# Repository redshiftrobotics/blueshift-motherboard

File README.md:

# blueshift-motherboard
Blueshift Robotics Motherboard Design Files

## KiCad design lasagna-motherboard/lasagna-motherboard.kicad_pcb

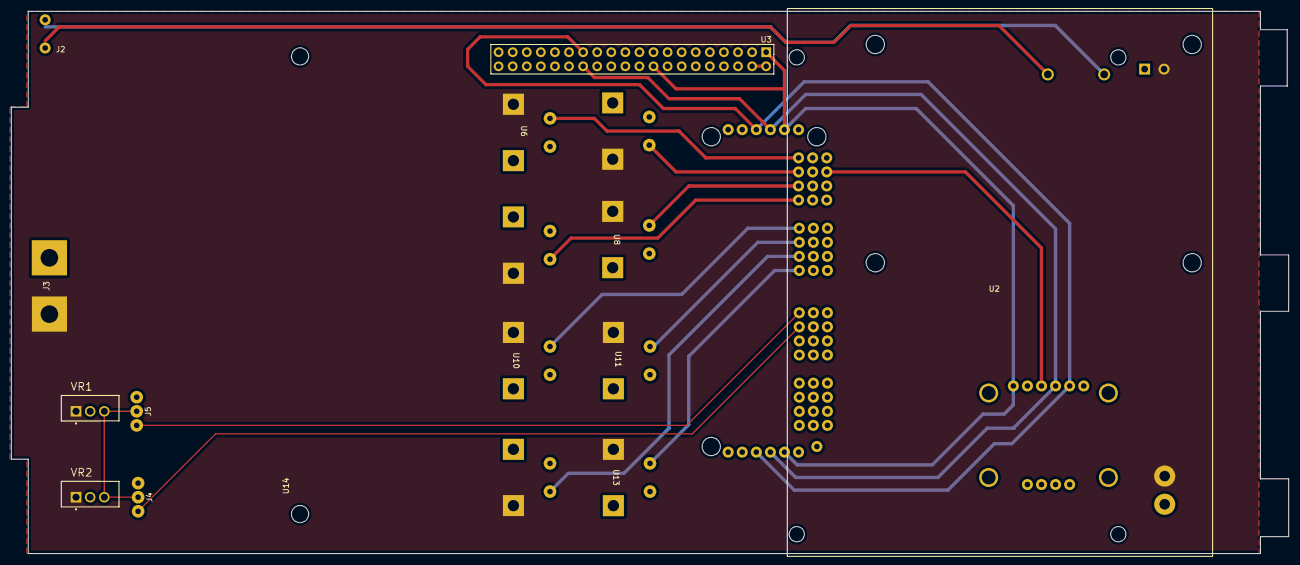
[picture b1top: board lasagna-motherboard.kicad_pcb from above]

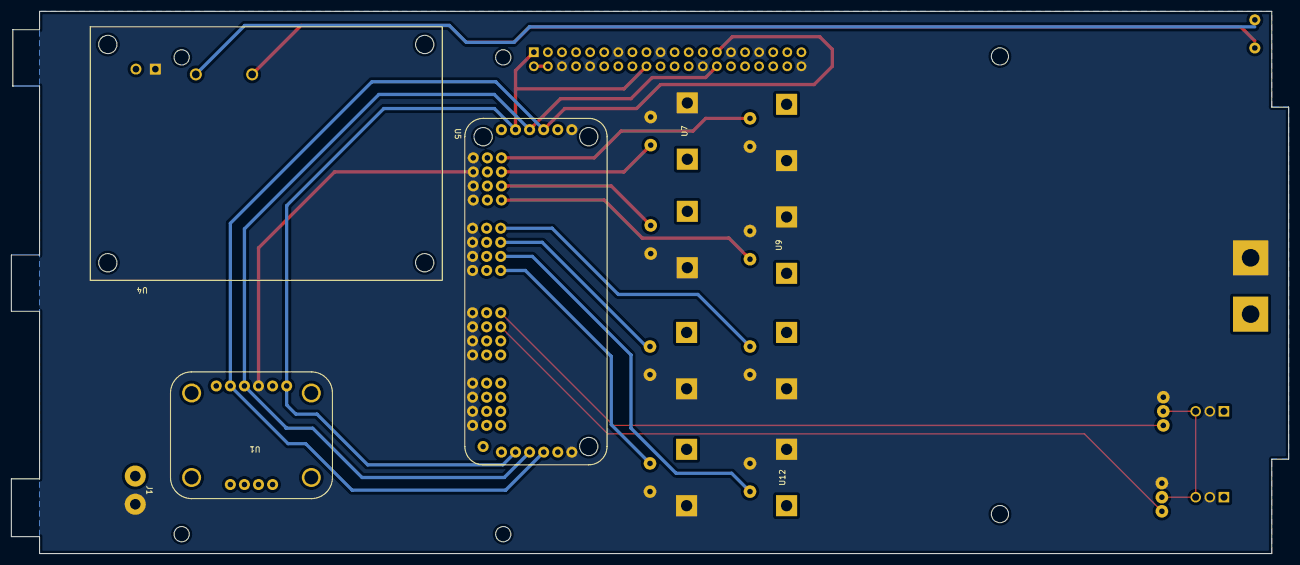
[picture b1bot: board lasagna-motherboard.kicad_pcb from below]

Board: 2 copper layers, 230.4 x 97.8 mm, 21 parts (7 on the bottom side), 18 nets.

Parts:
J1: Jetson_Power_Connector; Jetson Power Connector
J2: Fathom_X_Connector; FathomX_Connector
J3: Power_Connector
J4, J5: Servo_Connector; Servo PWM Connector
U1: Adafruit_BNO055_IMU
U2: Jetson_Xavier_NX_Mounting_Holes
U3: Jetson_Xavier_NX_Pins; Jetson_Xavier_NX_2X20_Pin_Header
U4: FathomX
U5: Adafruit_PCA9685_PWMGen
U6, U7, U8, U9, U10, U11, U12, U13: ESC
U14: ESC_Holder_Mounting_Holes; ESC Holder mounting Holes
VR1, VR2: 7805_TO-220_Voltage_Regulator; Voltage Regulator TO255

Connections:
+3V3: U1.5 (VIN), U3.1 (3V3), U3.17 (3V3), U5.5 (VCC), U5.11 (VCC)
+5V: J4.2 (VIN), J5.2 (VIN), U3.2 (5V), U3.4 (5V), VR1.3 (VOUT), VR2.3 (VOUT)
+12V: J1.1 (VIN), J3.1 (VIN), U4.4 (VIN), U6.1 (VIN), U7.1 (VIN), U8.1 (VIN), U9.1 (VIN), U10.1 (VIN), U11.1 (VIN), U12.1 (VIN), U13.1 (VIN), VR1.1 (VIN), VR2.1 (VIN)
GND: J1.2 (GND), J3.2 (GND), J4.3 (GND), J5.3 (GND), U1.7 (GND), U3.6 (GND), U3.9 (GND), U3.14 (GND), U3.20 (GND), U3.25 (GND), U3.30 (GND), U3.34 (GND), U3.39 (GND), U4.3 (GND), U5.1 (GND), U5.7 (GND), U5.15 (GND), U5.18 (GND), U5.21 (GND), U5.24 (GND), U5.27 (GND), U5.30 (GND), U5.33 (GND), U5.36 (GND), U5.39 (GND), U5.42 (GND), U5.45 (GND), U5.48 (GND), U5.51 (GND), U5.54 (GND), U5.57 (GND), U5.60 (GND), U6.2 (GND), U6.4 (PWM_GND), U7.2 (GND), U7.4 (PWM_GND), U8.2 (GND), U8.4 (PWM_GND), U9.2 (GND), U9.4 (PWM_GND), U10.2 (GND), U10.4 (PWM_GND), U11.2 (GND), U11.4 (PWM_GND), U12.2 (GND), U12.4 (PWM_GND), U13.2 (GND), U13.4 (PWM_GND), VR1.2 (GND), VR2.2 (GND)
unnamed: J2.1 (PL_L), U4.1 (PL_L)
unnamed: J2.2 (HV_SIG), U4.2 (HV_SIG)
unnamed: U1.8 (SDA), U3.27 (I2C0_SDA), U5.4 (SDA), U5.10 (SDA)
unnamed: U1.9 (SCL), U3.28 (I2C0_SCL), U5.3 (SCL), U5.9 (SCL)
unnamed: U5.13 (PWM0), U6.3 (PWM)
unnamed: U5.16 (PWM1), U7.3 (PWM)
unnamed: U5.19 (PWM2), U8.3 (PWM)
unnamed: U5.22 (PWM3), U9.3 (PWM)
unnamed: J5.1 (PWM), U5.37 (PWM8)
unnamed: J4.1 (PWM), U5.40 (PWM9)
unnamed: U5.25 (PWM4), U10.3 (PWM)
unnamed: U5.28 (PWM5), U11.3 (PWM)
unnamed: U5.31 (PWM6), U12.3 (PWM)
unnamed: U5.34 (PWM7), U13.3 (PWM)

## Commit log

2021-04-14 Test version control
2021-04-18 introducing Colin the Motherboard :)
2021-04-21 changed schematic symbol, begain schematic layout
2021-04-24 finish first pass at schematic, errors not fully resolved yet
2021-05-12 finish first draft of Colin 1.0, connect molex connectors directly, add capacitors but expect to solder directly to the ESCs, add 3V3 miniplane
2021-05-13 create active BOM
2021-05-13 Combine duplicate connectors, remove old test schematic file
2021-05-13 Update pcb board shape to make room for main power connector
2021-05-14 Revert "Update pcb board shape to make room for main power connector"
    This reverts commit 495c49e4263b1bc1385d283c099a491fd0e220ab.
2021-05-14 finish draft of Colin v1.0! Clear DRC violations, adjust silkscreen
2021-05-14 Add outjob files
2021-05-14 Update 2 pos connector component descriptions
2021-05-14 Add schematic symbols for jetson and esc mounting holes
2021-05-14 Remove mechanical components from BOM
2021-05-14 eliminate dumb part of 3v3 polygon
2021-05-14 Colin Motherboard v1.0 Release
    Update outjob files to combine gerbers and nc drill into one folder that can be uploaded
2021-05-14 Colin Motherboard v1.0 release
    Update prjpcb to have zip file as release target instead of altium cloud
2021-05-14 Colin Motherboard v1.0
    Update fabrication outjob to put combined gerber data in their own directory
2021-05-17 Remove silkscreen label from board outline layer
2021-10-31 Get rid of old files
2022-01-29 I just added the 5 volt linear regulator
2022-01-29 deleted some files
2022-05-12 Clean up PCB and Schematic
2022-08-10 Add .gitattributes
2022-12-31 Move to Old
    :0
2022-12-31 created lasagna file
2023-01-01 Add empty schematic library
2023-01-01 created IMU Schematic symbol
2023-01-01 added schematic symbol for FathomX and Jetson
2023-01-01 Add IMU Footprint
2023-01-02 Add PWM Gen Footprint an symbol
2023-01-02 Add U? to descriptor
2023-01-02 Add footprints for components
    Add footprints for ESC, FathomX Connector, Power Connector, Jetson 2x20 Pin Header and Jetson Mounting Holes
2023-01-02 Created the Jetson Pin, power connector, and ESCSymbols
2023-01-03 finished the schematic + created jetson power connector footprint
2023-01-03 Add PWM footprint
2023-01-03 created something
2023-01-04 Rezise pads of IMU, PWM controller and FathomX Connector
2023-01-20 added the servo connectors
